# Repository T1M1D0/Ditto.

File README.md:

Hello! This is a keyboard I created that uses Choc v2 switches (with a very nice case I know)

I used:<br>
https://github.com/MudkipMao/AliceKeyboardLayout/tree/master for the layout of the keys<br>
https://github.com/recursivenomad/ki-lime-pi-to-go for the rasperry pi pico footprint<br>
https://github.com/adamws/kle-ng to modify the layout and to generate the footprint seen in the kicad files<br>
https://peppe8o.com/raspberry-pi-pico-pinout/ for reference with the GPIO Pins<br>

I hope you enjoy my project!

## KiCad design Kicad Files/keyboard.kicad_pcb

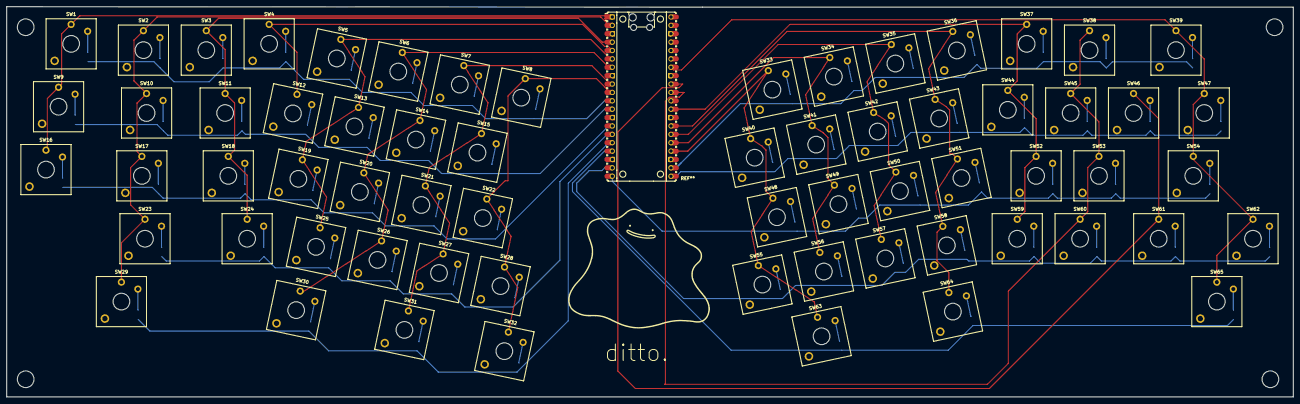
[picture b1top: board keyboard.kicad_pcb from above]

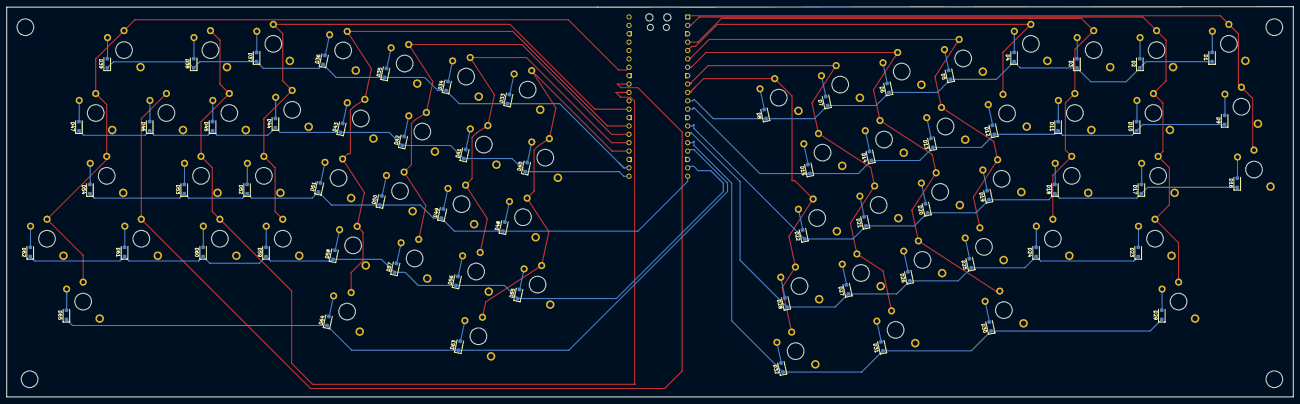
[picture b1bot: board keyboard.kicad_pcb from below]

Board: 2 copper layers, 389.9 x 118.2 mm, 130 parts (65 on the bottom side), 91 nets.

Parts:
D1, D2, D3, D4, D5, D6, D7, D8, D9, D10, D11, D12, D13, D14, D15, D16, D17, D18, D19, D20, D21, D22, D23, D24, D25, D26, D27, D28, D29, D30, D31, D32, D33, D34, D35, D36, D37, D38, D39, D40, D41, D42, D43, D44, D45, D46, D47, D48, D49, D50, D51, D52, D53, D54, D55, D56, D57, D58, D59, D60, D61, D62, D63, D64, D65: D; D_SOD-123F
SW1, SW2, SW3, SW4, SW5, SW6, SW7, SW8, SW9, SW11, SW12, SW13, SW14, SW15, SW16, SW18, SW19, SW20, SW21, SW22, SW24, SW25, SW26, SW27, SW28, SW33, SW34, SW35, SW36, SW37, SW38, SW40, SW41, SW42, SW43, SW44, SW45, SW46, SW48, SW49, SW50, SW51, SW52, SW53, SW55, SW56, SW57, SW58, SW59, SW60, SW62: SW_Push; SW_Kailh_Choc_V2_1.00u
SW10, SW29, SW30, SW61: SW_Push; SW_Kailh_Choc_V2_1.50u
SW17, SW39: SW_Push; SW_Kailh_Choc_V2_1.75u
SW23: SW_Push; SW_Kailh_Choc_V2_2.25u
SW31, SW54: SW_Push; SW_Kailh_Choc_V2_2.00u
SW32, SW47, SW64, SW65: SW_Push; SW_Kailh_Choc_V2_1.25u
SW63: SW_Push; SW_Kailh_Choc_V2_2.50u

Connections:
COL0: SW1.1, SW9.1, SW16.1
COL1: SW2.1, SW10.1, SW17.1, SW23.1, SW29.1
COL2: SW3.1, SW11.1, SW18.1, SW24.1
COL3: SW4.1, SW12.1
COL4: SW5.1, SW13.1, SW19.1, SW25.1
COL5: SW6.1, SW14.1, SW20.1, SW26.1, SW30.1
COL6: SW7.1, SW15.1, SW21.1, SW27.1, SW31.1
COL7: SW8.1, SW22.1, SW28.1, SW32.1
COL8: SW33.1, SW40.1, SW48.1, SW55.1, SW63.1
COL9: SW34.1, SW41.1, SW49.1, SW56.1
COL10: SW35.1, SW42.1, SW50.1, SW57.1
COL11: SW36.1, SW43.1, SW51.1, SW58.1, SW64.1
COL12: SW37.1, SW44.1, SW52.1, SW59.1
COL13: SW38.1, SW45.1, SW53.1, SW60.1
COL14: SW46.1, SW61.1
COL15: SW39.1, SW47.1, SW54.1, SW62.1, SW65.1
unnamed: D1.2 (A), SW1.2
unnamed: D2.2 (A), SW2.2
unnamed: D3.2 (A), SW3.2
unnamed: D4.2 (A), SW4.2
unnamed: D5.2 (A), SW5.2
unnamed: D6.2 (A), SW6.2
unnamed: D7.2 (A), SW7.2
unnamed: D8.2 (A), SW8.2
unnamed: D9.2 (A), SW9.2
unnamed: D10.2 (A), SW10.2
unnamed: D11.2 (A), SW11.2
unnamed: D12.2 (A), SW12.2
unnamed: D13.2 (A), SW13.2
unnamed: D14.2 (A), SW14.2
unnamed: D15.2 (A), SW15.2
unnamed: D16.2 (A), SW16.2
unnamed: D17.2 (A), SW17.2
unnamed: D18.2 (A), SW18.2
unnamed: D19.2 (A), SW19.2
unnamed: D20.2 (A), SW20.2
unnamed: D21.2 (A), SW21.2
unnamed: D22.2 (A), SW22.2
unnamed: D23.2 (A), SW23.2
unnamed: D24.2 (A), SW24.2
unnamed: D25.2 (A), SW25.2
unnamed: D26.2 (A), SW26.2
unnamed: D27.2 (A), SW27.2
unnamed: D28.2 (A), SW28.2
unnamed: D29.2 (A), SW29.2
unnamed: D30.2 (A), SW30.2
unnamed: D31.2 (A), SW31.2
unnamed: D32.2 (A), SW32.2
unnamed: D33.2 (A), SW33.2
unnamed: D34.2 (A), SW34.2
unnamed: D35.2 (A), SW35.2
unnamed: D36.2 (A), SW36.2
unnamed: D37.2 (A), SW37.2
unnamed: D38.2 (A), SW38.2
unnamed: D39.2 (A), SW39.2
unnamed: D40.2 (A), SW40.2
unnamed: D41.2 (A), SW41.2
unnamed: D42.2 (A), SW42.2
unnamed: D43.2 (A), SW43.2
unnamed: D44.2 (A), SW44.2
unnamed: D45.2 (A), SW45.2
unnamed: D46.2 (A), SW46.2
unnamed: D47.2 (A), SW47.2
unnamed: D48.2 (A), SW48.2
unnamed: D49.2 (A), SW49.2
unnamed: D50.2 (A), SW50.2
unnamed: D51.2 (A), SW51.2
unnamed: D52.2 (A), SW52.2
unnamed: D53.2 (A), SW53.2
unnamed: D54.2 (A), SW54.2
unnamed: D55.2 (A), SW55.2
unnamed: D56.2 (A), SW56.2
unnamed: D57.2 (A), SW57.2
unnamed: D58.2 (A), SW58.2
unnamed: D59.2 (A), SW59.2
unnamed: D60.2 (A), SW60.2
unnamed: D61.2 (A), SW61.2
unnamed: D62.2 (A), SW62.2
unnamed: D63.2 (A), SW63.2
unnamed: D64.2 (A), SW64.2
unnamed: D65.2 (A), SW65.2
ROW0: D1.1 (K), D2.1 (K), D3.1 (K), D4.1 (K), D5.1 (K), D6.1 (K), D7.1 (K), D8.1 (K)
ROW1: D9.1 (K), D10.1 (K), D11.1 (K), D12.1 (K), D13.1 (K), D14.1 (K), D15.1 (K)
ROW2: D16.1 (K), D17.1 (K), D18.1 (K), D19.1 (K), D20.1 (K), D21.1 (K), D22.1 (K)
ROW3: D23.1 (K), D24.1 (K), D25.1 (K), D26.1 (K), D27.1 (K), D28.1 (K)
ROW4: D29.1 (K), D30.1 (K), D31.1 (K), D32.1 (K)
ROW5: D33.1 (K), D34.1 (K), D35.1 (K), D36.1 (K), D37.1 (K), D38.1 (K), D39.1 (K)
ROW6: D40.1 (K), D41.1 (K), D42.1 (K), D43.1 (K), D44.1 (K), D45.1 (K), D46.1 (K), D47.1 (K)
ROW7: D48.1 (K), D49.1 (K), D50.1 (K), D51.1 (K), D52.1 (K), D53.1 (K), D54.1 (K)
ROW8: D55.1 (K), D56.1 (K), D57.1 (K), D58.1 (K), D59.1 (K), D60.1 (K), D61.1 (K), D62.1 (K)
ROW9: D63.1 (K), D64.1 (K), D65.1 (K)
